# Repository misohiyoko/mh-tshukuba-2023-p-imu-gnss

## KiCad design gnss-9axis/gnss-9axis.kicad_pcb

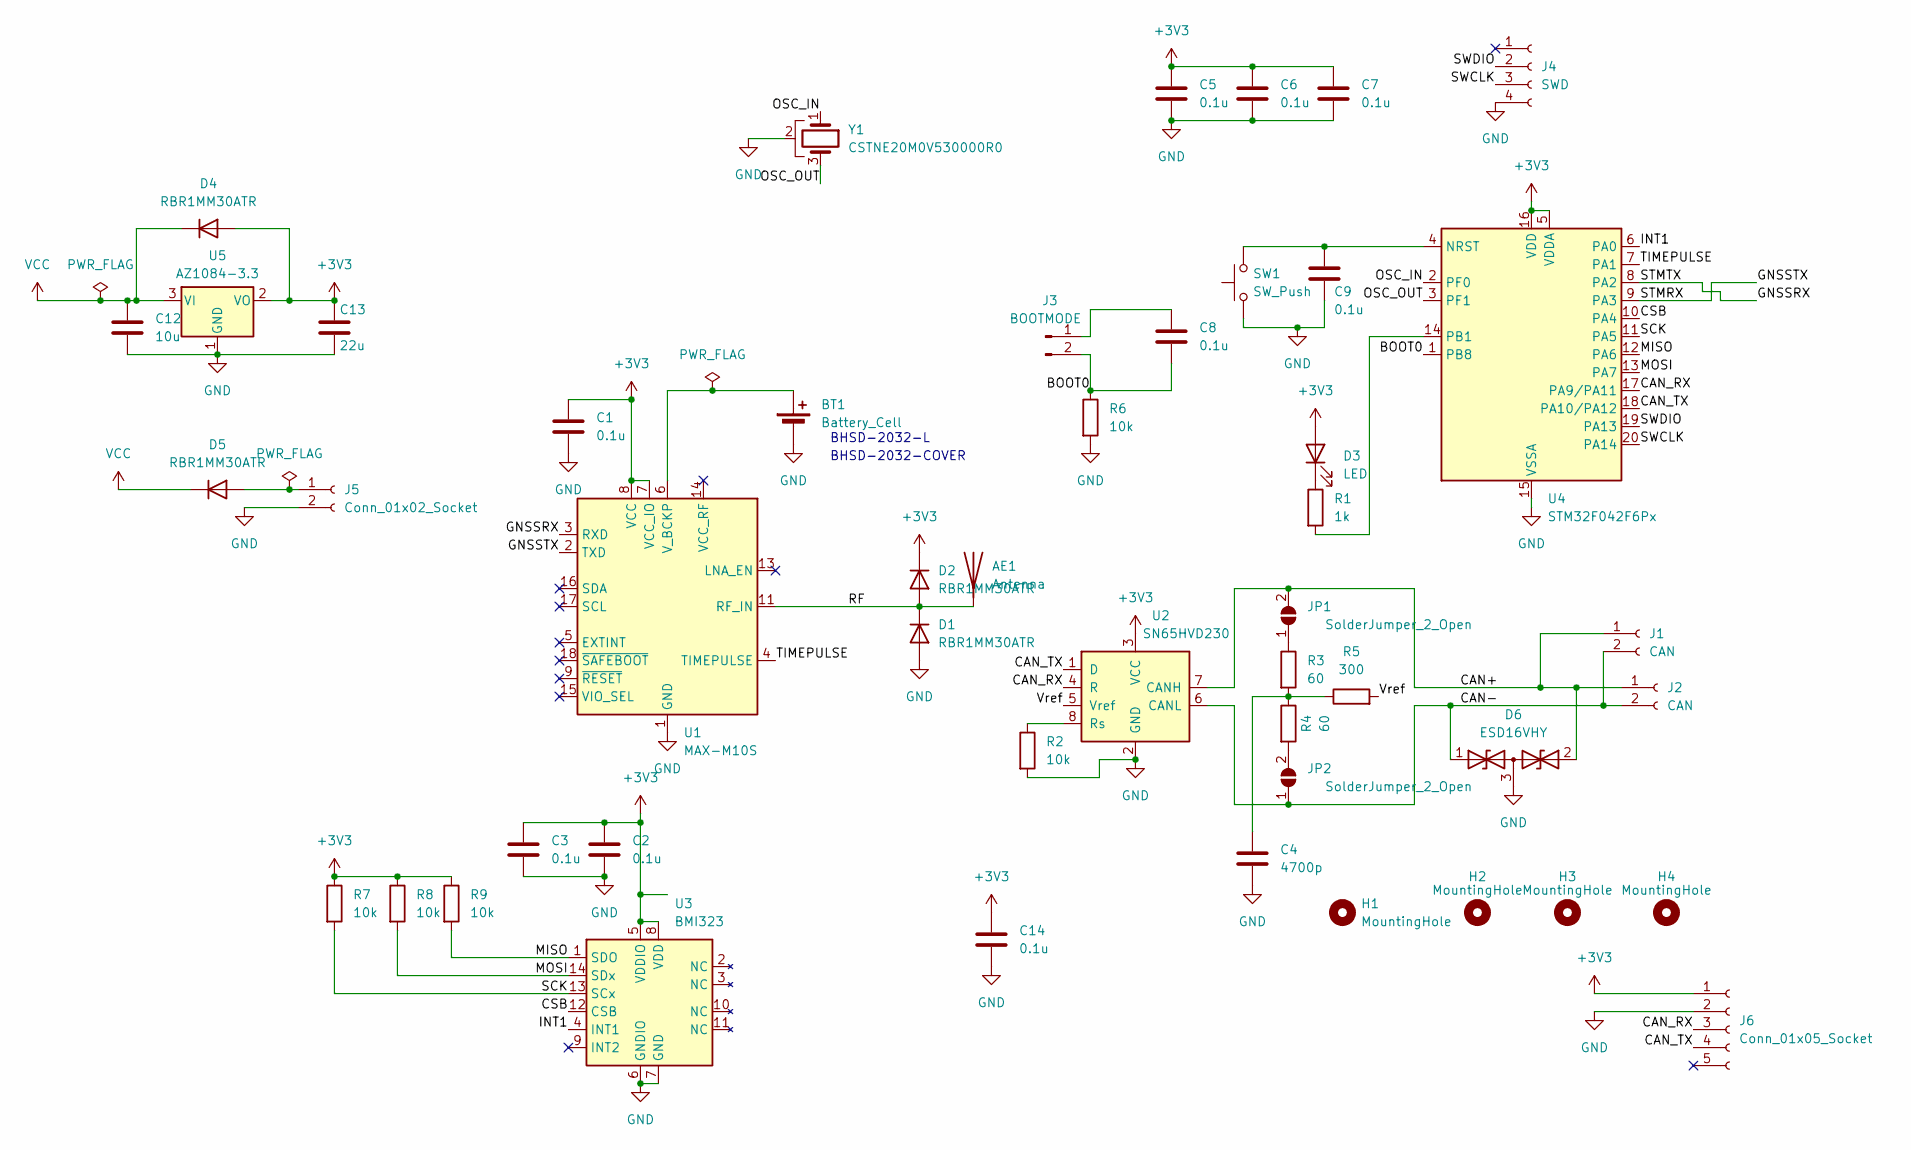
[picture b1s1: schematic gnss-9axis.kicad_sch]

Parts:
AE1: Antenna; CGGBP.35.6.A.02
BT1: Battery_Cell; CR1220
C1, C2, C3, C5, C6, C7, C8, C9, C14: 0.1u; C_0603_1608Metric_Pad1.08x0.95mm_HandSolder
C4: 4700p; C_0603_1608Metric_Pad1.08x0.95mm_HandSolder
C12: 10u; C_0603_1608Metric_Pad1.08x0.95mm_HandSolder
C13: 22u; C_0603_1608Metric_Pad1.08x0.95mm_HandSolder
D1, D2, D4, D5: RBR1MM30ATR; D_SOD-123F
D3: LED; LED_0603_1608Metric_Pad1.05x0.95mm_HandSolder
D6: ESD16VHY; SOT-23-3
H1, H2, H3, H4: MountingHole; MountingHole_3.2mm_M3_ISO14580
J1, J2: CAN; JST_XH_B2B-XH-AM_1x02_P2.50mm_Vertical
J3: BOOTMODE; PinHeader_1x02_P2.54mm_Vertical
J4: SWD; PinHeader_1x04_P2.54mm_Vertical
J5: Conn_01x02_Socket; PinHeader_1x02_P2.54mm_Vertical
J6: Conn_01x05_Socket; PinHeader_1x05_P2.54mm_Vertical
JP1, JP2: SolderJumper_2_Open; SolderJumper-2_P1.3mm_Open_TrianglePad1.0x1.5mm
R1: 1k; R_0402_1005Metric_Pad0.72x0.64mm_HandSolder
R2, R6, R7, R8, R9: 10k; R_0402_1005Metric_Pad0.72x0.64mm_HandSolder
R3, R4: 60; R_0402_1005Metric_Pad0.72x0.64mm_HandSolder
R5: 300; R_0402_1005Metric_Pad0.72x0.64mm_HandSolder
SW1: SW_Push; SW_Push_1P1T_NO_6x6mm_H9.5mm
U1: MAX-M10S; ublox_MAX
U2: SN65HVD230; SOIC-8_3.9x4.9mm_P1.27mm
U3: BMI323; Bosch_LGA-14_3x2.5mm_P0.5mm
U4: STM32F042F6Px; TSSOP-20_4.4x6.5mm_P0.65mm
U5: AZ1084-3.3; TO-252-2
Y1: CSTNE20M0V530000R0; Resonator_SMD_Murata_CSTxExxV-3Pin_3.0x1.1mm_HandSoldering

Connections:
+3V3: C1.1, C2.1, C3.1, C5.1, C6.1, C7.1, C13.1, C14.1, D2.1 (K), D3.2 (A), D4.2 (A), J6.1, R7.1, R8.1, R9.1, U1.7 (VCC_IO), U1.8 (VCC), U2.3 (VCC), U3.5 (VDDIO), U3.8 (VDD), U4.5 (VDDA), U4.16 (VDD), U5.2 (VO)
/BOOT0: C8.2, J3.2, R6.1, U4.1 (PB8)
/CAN+: D6.2 (A2), J1.1, J2.1, JP1.2 (B), U2.7 (CANH)
/CAN-: D6.1 (A1), J1.2, J2.2, JP2.1 (A), U2.6 (CANL)
/CAN_RX: J6.3, U2.4 (R), U4.17 (PA9/PA11)
/CAN_TX: J6.4, U2.1 (D), U4.18 (PA10/PA12)
/CSB: U3.12 (CSB), U4.10 (PA4)
/GNSSRX: U1.3 (RXD), U4.8 (PA2)
/GNSSTX: U1.2 (TXD), U4.9 (PA3)
/INT1: U3.4 (INT1), U4.6 (PA0)
/MISO: R9.2, U3.1 (SDO), U4.12 (PA6)
/MOSI: R8.2, U3.14 (SDx), U4.13 (PA7)
/OSC_IN: U4.2 (PF0), Y1.1
/OSC_OUT: U4.3 (PF1), Y1.3
/RF: AE1.1 (A), D1.1 (K), D2.2 (A), U1.11 (RF_IN)
/SCK: R7.2, U3.13 (SCx), U4.11 (PA5)
/SWCLK: J4.3, U4.20 (PA14)
/SWDIO: J4.2, U4.19 (PA13)
/TIMEPULSE: U1.4 (TIMEPULSE), U4.7 (PA1)
/Vref: R5.2, U2.5 (Vref)
GND: BT1.2 (-), C1.2, C2.2, C3.2, C4.2, C5.2, C6.2, C7.2, C9.2, C12.2, C13.2, C14.2, D1.2 (A), D6.3 (common), J4.4, J5.2, J6.2, R2.2, R6.2, SW1.1, U1.1 (GND), U1.10 (GND), U1.12 (GND), U2.2 (GND), U3.6 (GNDIO), U3.7 (GND), U4.15 (VSSA), U5.1 (GND), Y1.2
unnamed: BT1.1 (+), U1.6 (V_BCKP)
unnamed: C4.1, R3.2, R4.1, R5.1
unnamed: D3.1 (K), R1.1
unnamed: D5.2 (A), J5.1
unnamed: C8.1, J3.1
unnamed: JP1.1 (A), R3.1
unnamed: JP2.2 (B), R4.2
unnamed: R2.1, U2.8 (Rs)
unnamed: C9.1, SW1.2, U4.4 (NRST)
unnamed: R1.2, U4.14 (PB1)
VCC: C12.1, D4.1 (K), D5.1 (K), U5.3 (VI)

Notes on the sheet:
BHSD-2032-COVER
BHSD-2032-L

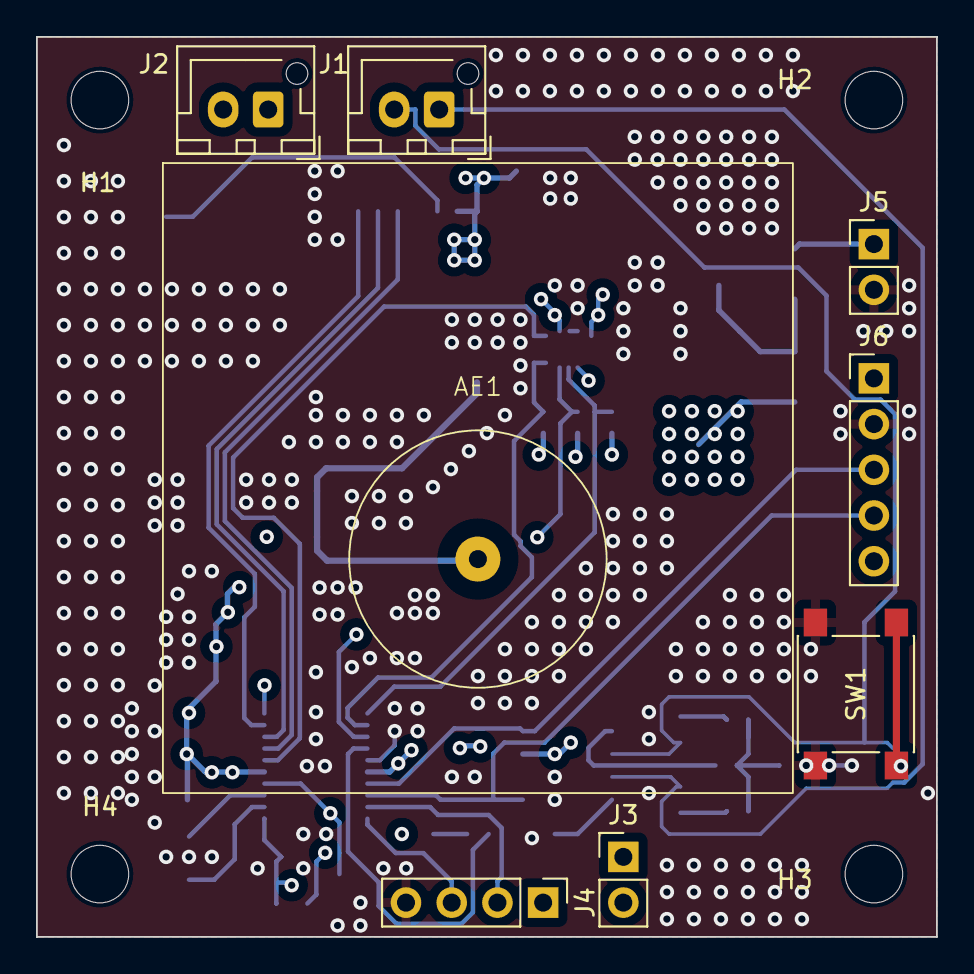
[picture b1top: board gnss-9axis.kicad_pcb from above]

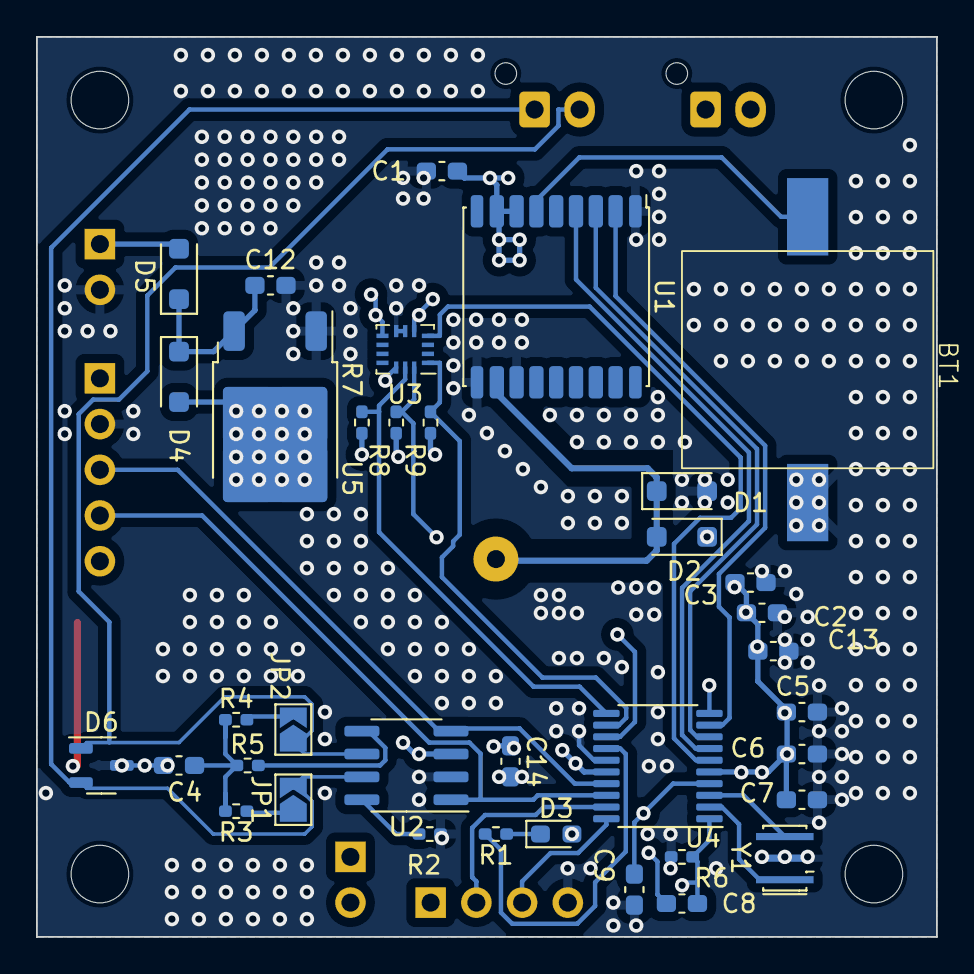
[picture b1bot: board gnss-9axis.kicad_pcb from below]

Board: 4 copper layers, 50.0 x 50.0 mm, 48 parts (36 on the bottom side), 32 nets.

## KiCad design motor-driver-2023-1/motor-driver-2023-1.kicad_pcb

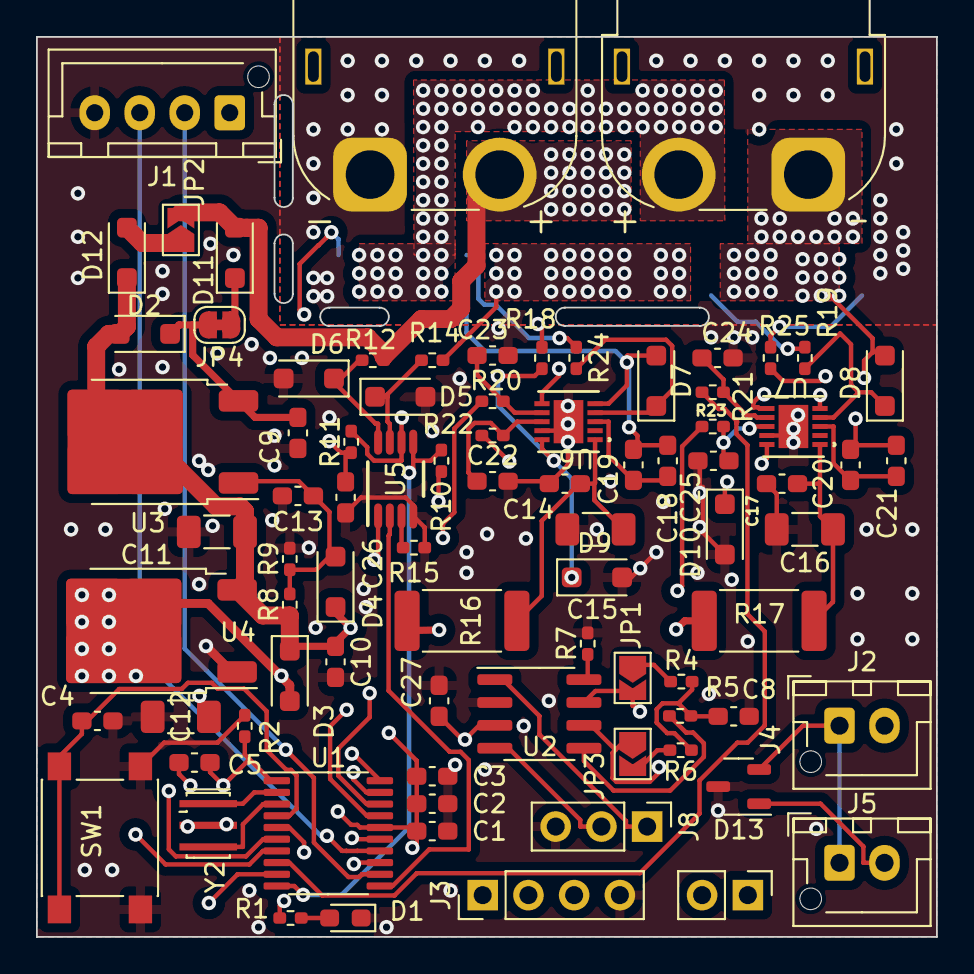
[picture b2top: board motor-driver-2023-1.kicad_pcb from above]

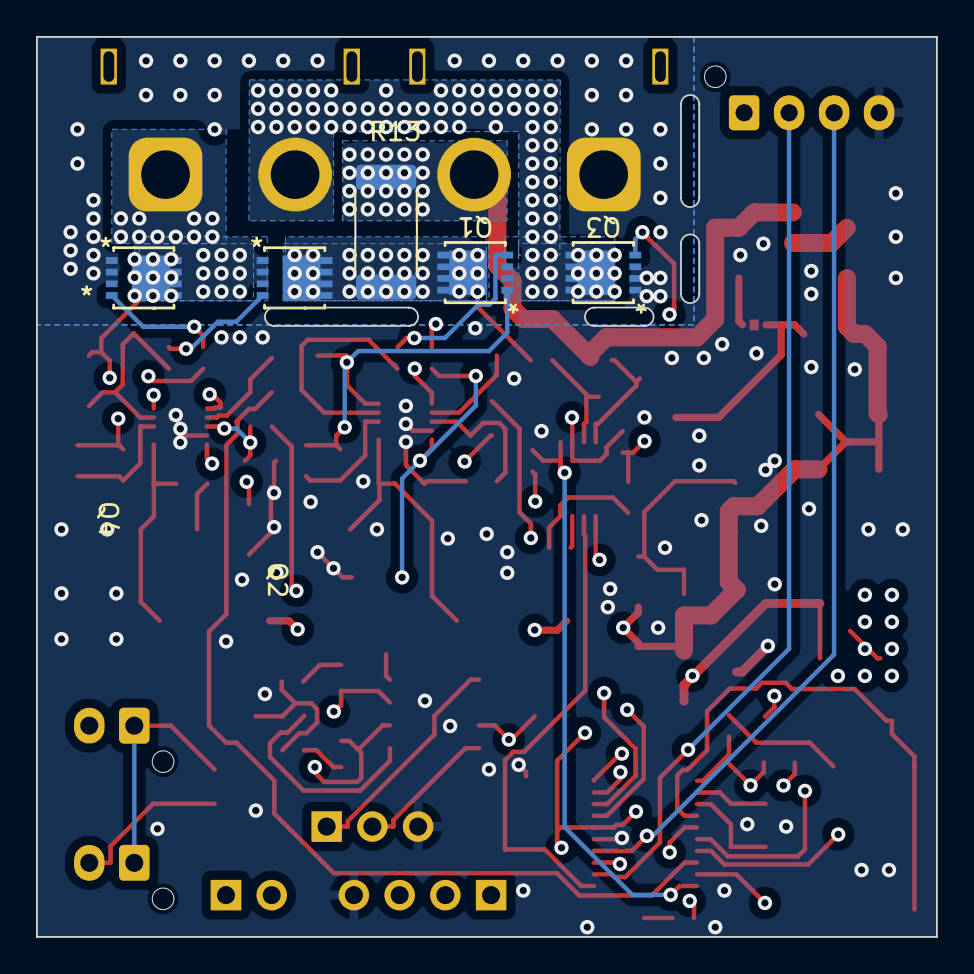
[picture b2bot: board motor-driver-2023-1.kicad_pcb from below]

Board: 4 copper layers, 50.0 x 50.0 mm, 87 parts (5 on the bottom side), 56 nets.

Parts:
C1, C2, C3, C4, C5, C9, C26, C27: 0.1u; C_0603_1608Metric_Pad1.08x0.95mm_HandSolder
C8: 4700p; C_0603_1608Metric_Pad1.08x0.95mm_HandSolder
C10, C13, C19, C20: 1u; C_0603_1608Metric_Pad1.08x0.95mm_HandSolder
C11, C15, C16: 10u; C_1206_3216Metric_Pad1.33x1.80mm_HandSolder
C12: 22u; C_1206_3216Metric_Pad1.33x1.80mm_HandSolder
C14, C17, C18, C21: 1000p; C_0603_1608Metric_Pad1.08x0.95mm_HandSolder
C22, C23, C24, C25: 47p; C_0603_1608Metric_Pad1.08x0.95mm_HandSolder
D1: LED; LED_0603_1608Metric_Pad1.05x0.95mm_HandSolder
D2, D3, D4, D7, D8, D9, D10, D11, D12: RBR1MM30ATR; D_SOD-123F
D5, D6: KDZVTR30B; D_SOD-123F
D13: ESD16VHY; SOT-23-3
J1: Encoder; JST_XH_B4B-XH-AM_1x04_P2.50mm_Vertical
J2, J5: CAN; JST_XH_B2B-XH-AM_1x02_P2.50mm_Vertical
J3: SWD; PinHeader_1x04_P2.54mm_Vertical
J4: BOOTMODE; PinHeader_1x02_P2.54mm_Vertical
J6: BATT; AMASS_XT60PW-M_1x02_P7.20mm_Horizontal
J8: Conn_01x03_Socket; PinHeader_1x03_P2.54mm_Vertical
JP1, JP2, JP3: SolderJumper_2_Open; SolderJumper-2_P1.3mm_Open_TrianglePad1.0x1.5mm
JP4: SolderJumper_2_Bridged; SolderJumper-2_P1.3mm_Bridged_RoundedPad1.0x1.5mm
M1: Motor_DC; AMASS_XT60PW-F_1x02_P7.20mm_Horizontal
Q1, Q2, Q3, Q4: Q_NMOS_DGS; TSON Advance_TOS
R1: 1k; R_0402_1005Metric_Pad0.72x0.64mm_HandSolder
R2, R7, R10, R11: 10k; R_0402_1005Metric_Pad0.72x0.64mm_HandSolder
R4, R6: 60; R_0402_1005Metric_Pad0.72x0.64mm_HandSolder
R5: 300; R_0402_1005Metric_Pad0.72x0.64mm_HandSolder
R8: 240; R_0402_1005Metric_Pad0.72x0.64mm_HandSolder
R9: 1.2k; R_0402_1005Metric_Pad0.72x0.64mm_HandSolder
R12, R14, R20, R21, R22, R23: 10; R_0402_1005Metric_Pad0.72x0.64mm_HandSolder
R13: 1m; R_2512_6332Metric_Pad1.40x3.35mm_HandSolder
R15: 25k; R_0402_1005Metric_Pad0.72x0.64mm_HandSolder
R16, R17: 1; R_2512_6332Metric_Pad1.40x3.35mm_HandSolder
R18, R19, R24, R25: 220; R_0402_1005Metric_Pad0.72x0.64mm_HandSolder
SW1: SW_Push; SW_Push_1P1T_NO_6x6mm_H9.5mm
U1: STM32F042F6Px; TSSOP-20_4.4x6.5mm_P0.65mm
U2: SN65HVD230; SOIC-8_3.9x4.9mm_P1.27mm
U3: LM317_TO-252; TO-252-2
U4: AZ1084-3.3; TO-252-2
U5: INA301A1IDGKR; DGK0008A_L
U6, U7: LM5108DRCR; DRC10_1P65X2P40_TEX
Y2: CSTNE20M0V530000R0; Resonator_SMD_Murata_CSTxExxV-3Pin_3.0x1.1mm_HandSoldering

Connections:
+24V: D11.2 (A), J6.2, JP2.2 (B), R12.1, R13.1
/BOOT0: C5.2, J4.2, R2.1, U1.1 (PB8)
/CAN+: D13.2 (A2), J2.1, J5.1, JP1.2 (B), U2.7 (CANH)
/CAN-: D13.1 (A1), J2.2, J5.2, JP3.1 (A), U2.6 (CANL)
/CAN_RX: J8.2, U1.17 (PA9/PA11), U2.4 (R)
/CAN_TX: J8.1, U1.18 (PA10/PA12), U2.1 (D)
/ENC_1: J1.2, U1.12 (PA6)
/ENC_2: J1.3, U1.14 (PB1)
/OSC_IN: U1.2 (PF0), Y2.1
/OSC_OUT: U1.3 (PF1), Y2.3
/SWCLK: J3.3, U1.20 (PA14)
/SWDIO: J3.2, U1.19 (PA13)
/Vref: R5.2, U2.5 (Vref)
/full_bridge/EN: R11.2, U5.6 (ALERT_N), U6.6 (EN), U7.6 (EN)
/full_bridge/HI1: R20.1, U1.6 (PA0)
/full_bridge/HI2: R21.1, U1.8 (PA2)
/full_bridge/LI1: R22.2, U1.7 (PA1)
/full_bridge/LI2: R23.2, U1.9 (PA3)
/full_bridge/MOut1: C18.2, C19.2, D7.2 (A), M1.2 (-), Q1.3 (S), Q3.1 (D), U6.5 (HS)
/full_bridge/MOut2: C20.2, C21.2, D8.2 (A), M1.1 (+), Q2.3 (S), Q4.1 (D), U7.5 (HS)
/full_bridge/RESET: R10.2, U1.10 (PA4), U5.5 (RESET)
/full_bridge/VOUT: U1.11 (PA5), U5.2 (OUT)
GND: C1.2, C2.2, C3.2, C4.2, C8.2, C9.2, C10.2, C11.2, C12.2, C13.2, C14.2, C15.2, C16.2, C17.2, C22.2, C23.2, C24.2, C25.2, C26.2, C27.2, D1.1 (K), D5.2 (A), D6.2 (A), D9.2 (A), D10.2 (A), D13.3 (common), J1.4, J3.4, J6.1, J8.3, Q3.3 (S), Q4.3 (S), R2.2, R7.2, R9.2, R15.2, SW1.1, U1.15 (VSSA), U2.2 (GND), U4.1 (GND), U5.4 (GND), U6.9 (VSS), U6.11 (EPAD), U7.9 (VSS), U7.11 (EPAD), Y2.2
unnamed: C8.1, R4.2, R5.1, R6.1
unnamed: D1.2 (A), R1.2
unnamed: C9.1, D2.1 (K), JP4.2 (B), U3.3 (VI)
unnamed: C13.1, D4.2 (A), R8.2, R9.1, U3.1 (ADJ)
unnamed: D5.1 (K), R14.2, U5.7 (IN-)
unnamed: D6.1 (K), R12.2, U5.8 (IN+)
unnamed: D7.1 (K), R18.1, U6.4 (HO)
unnamed: D8.1 (K), R19.1, U7.4 (HO)
unnamed: D9.1 (K), R24.1, U6.10 (LO)
unnamed: D10.1 (K), R25.1, U7.10 (LO)
unnamed: D11.1 (K), JP4.1 (A)
unnamed: D12.2 (A), JP2.1 (A)
unnamed: JP1.1 (A), R4.1
unnamed: JP3.2 (B), R6.2
unnamed: Q1.1 (D), Q2.1 (D), R13.2, R14.1
unnamed: Q1.2 (G), R18.2
unnamed: Q2.2 (G), R19.2
unnamed: Q3.2 (G), R24.2
unnamed: Q4.2 (G), R25.2
unnamed: C4.1, SW1.2, U1.4 (NRST)
unnamed: R1.1, U1.13 (PA7)
unnamed: R7.1, U2.8 (Rs)
unnamed: R15.1, U5.3 (LIMIT)
unnamed: C18.1, C19.1, U6.3 (HB)
unnamed: C23.1, R20.2, U6.7 (HI)
unnamed: C22.1, R22.1, U6.8 (LI)
unnamed: C14.1, C15.1, R16.2, U6.1 (VDD)
unnamed: C20.1, C21.1, U7.3 (HB)
unnamed: C24.1, R21.2, U7.7 (HI)
unnamed: C25.1, R23.1, U7.8 (LI)
unnamed: C16.1, C17.1, R17.2, U7.1 (VDD)
VBUS: C10.1, C11.1, D2.2 (A), D3.1 (K), D4.1 (K), D12.1 (K), R8.1, R16.1, R17.1, U3.2 (VO), U4.3 (VI)
VDD: C1.1, C2.1, C3.1, C5.1, C12.1, C26.1, C27.1, D3.2 (A), J1.1, J4.1, R10.1, R11.1, U1.5 (VDDA), U1.16 (VDD), U2.3 (VCC), U4.2 (VO), U5.1 (VS)
